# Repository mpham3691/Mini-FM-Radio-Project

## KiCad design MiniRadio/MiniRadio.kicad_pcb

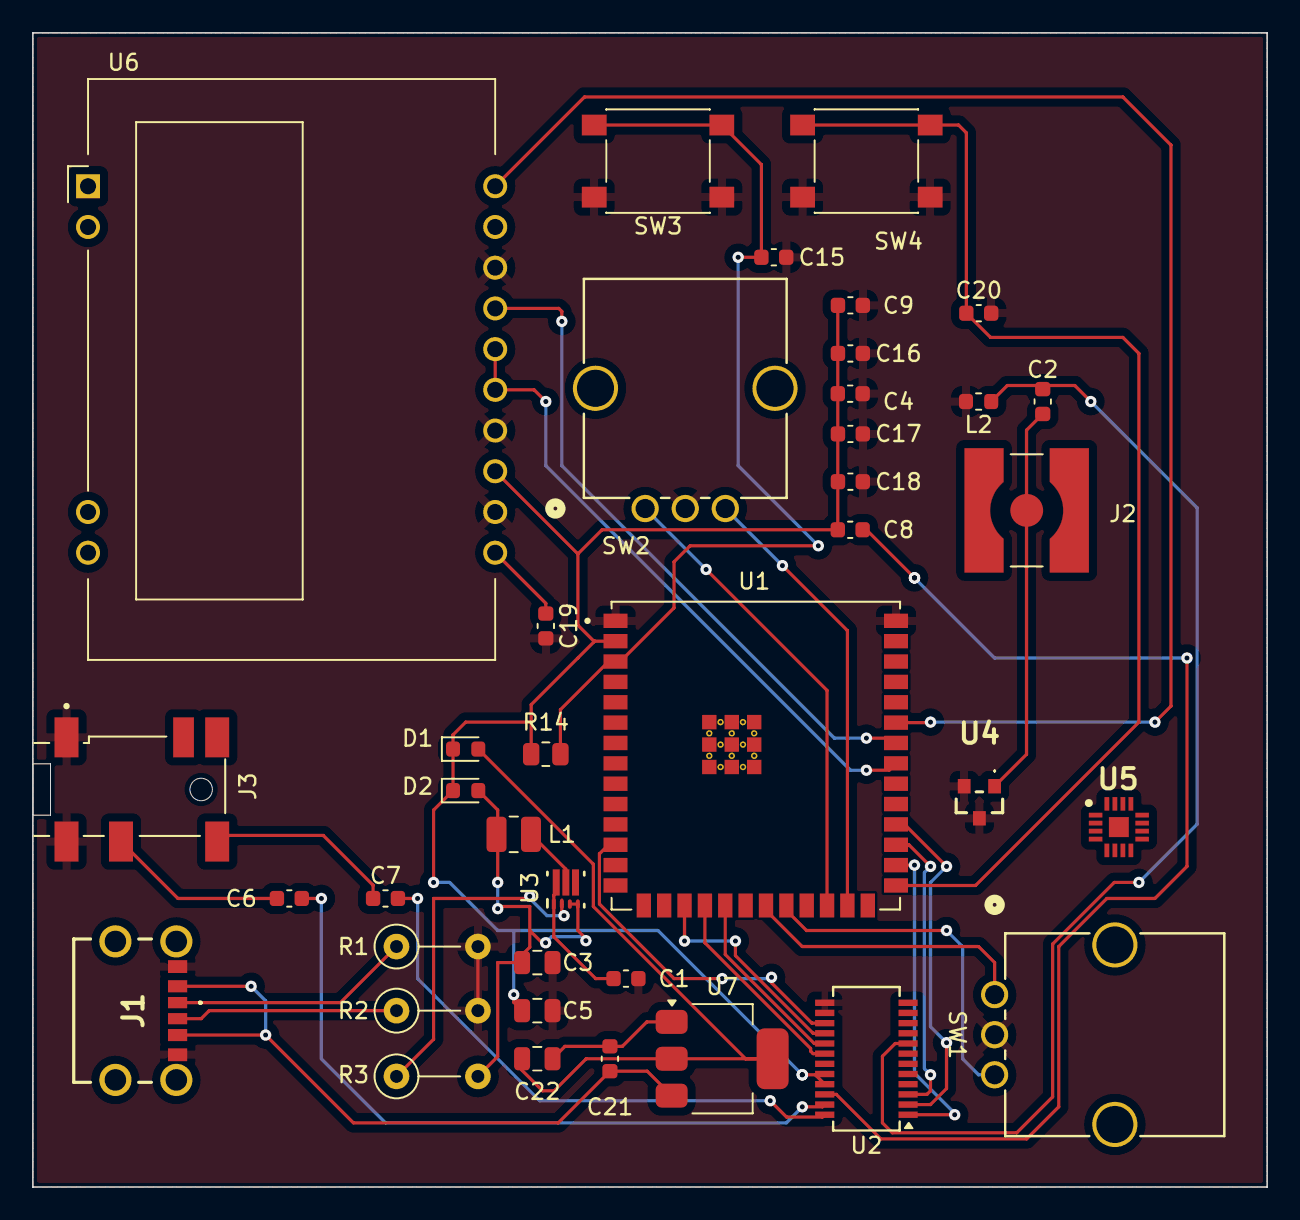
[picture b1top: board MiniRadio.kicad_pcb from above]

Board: 2 copper layers, 77.0 x 72.0 mm, 39 parts (0 on the bottom side), 35 nets.

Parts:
C1: 10u; C_0603_1608Metric
C2: 1n; C_0603_1608Metric
C3: 22u; C_0805_2012Metric
C4, C15, C17, C20: 0.1u; C_0603_1608Metric
C5, C22: 10u; C_0805_2012Metric
C6, C7: 4.7u; C_0603_1608Metric
C8: 22n; C_0603_1608Metric
C9, C21: 100n; C_0603_1608Metric
C16, C18, C19: 1u; C_0603_1608Metric
D1, D2: D_Schottky; D_0603_1608Metric
J1: USB_C_Receptacle_USB2.0; 2171750001
J2: SMA; LINX_CONSMA002-SMD-G-T
J3: 54-00178; TENSILITY_54-00178
L1: 470n; L_1008_2520Metric
L2: 56n; L_0603_1608Metric
R1, R2: 5.1k; R_Axial_DIN0207_L6.3mm_D2.5mm_P5.08mm_Vertical
R3: 1M; R_Axial_DIN0207_L6.3mm_D2.5mm_P5.08mm_Vertical
R14: 10k; R_0805_2012Metric
SW1: Freq_Tune; PEC12R-4XXXF-NXXXX_BRN
SW2: Volume_Tune; PEC12R-4XXXF-NXXXX_BRN
SW3: Reset; SW_SPST_PTS645
SW4: Boot; SW_SPST_PTS645
U1: ESP32-S3-WROOM-1; XCVR_ESP32-S3-WROOM-1U-N4
U2: Si4735-D60-GU; SSOP-24_3.9x8.7mm_P0.635mm
U3: RLT0007A
U4: D1213A01SO7
U5: QFN50P300X300X80-17N
U6: EA_DOGS164-A; EA_DOGS104X-A
U7: LD1117S33TR_SOT223; SOT-223-3_TabPin2

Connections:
+3.3V: C4.1, C5.1, C8.2, C9.1, C16.1, C17.1, C18.1, D1.1 (K), D2.1 (K), R14.1, U1.2 (3V3), U2.20 (VD), U2.21 (VA), U6.13 (VDD)
+5V: C21.1, J1.A9 (VBUS), J1.B9 (VBUS), U7.3 (VI)
/BATT_SUPPLY: C3.1, D2.2 (A), L1.2, R3.2, U3.3 (FB), U3.4 (VOS)
/DFS_RADIO: U1.30 (SPIDQS/GPIO37/FSPIQ/SUBSPIQ), U2.2 (DFS)
/DOUT_RADIO: U1.28 (SPIIO6/GPIO35/FSPID/SUBSPID), U2.1 (DOUT)
/FMI: C2.2, L2.1, U2.8 (FMI)
/FREQ_A: SW1.A, U1.21 (GPIO13/TOUCH13/ADC2_CH2/FSPIQ/FSPIIO7/S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)
/FREQ_B: SW1.B, U1.22 (GPIO14/TOUCH14/ADC2_CH3/FSPIWP/FSPIDQS/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)
/GPO3_RADIO: U1.29 (SPIIO7/GPIO36/FSPICLK/SUBSPICLK), U2.3 (GPO3/[DCLK])
/LOUT: C7.2, U2.24 (LOUT/[DFS])
/ROUT: C6.2, U2.23 (ROUT/[DOUT])
/RST_LCD: U1.35 (MTMS/GPIO42), U6.20 (~RST)
/RST_RADIO: U1.12 (GPIO8/TOUCH8/ADC1_CH7/SUBSPICS1), U2.15 (~RST)
/SCLK_LCD: U1.34 (MTDI/GPIO41/CLK_OUT1), U6.17 (SCLK)
/SCLK_RADIO: U1.19 (GPIO11/TOUCH11/ADC2_CH0/FSPID/FSPIIO5/S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), U2.17 (SCLK)
/SDIO_LCD: U1.33 (MTDO/GPIO40/CLK_OUT2), U6.15 (SOD), U6.16 (SID)
/SDIO_RADIO: U1.18 (GPIO10/TOUCH10/ADC1_CH9/FSPICS0/FSPIIO4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), U2.18 (SDIO)
/SEN_RADIO: U1.17 (GPIO9/TOUCH9/ADC1_CH8/FSPIHD/SUBSPIHD), U2.16 (~SEN)
/USB_SUPPLY: C22.1, D1.2 (A), U7.2 (VO)
/VOL_A: SW2.A, U1.24 (GPIO47/SPICLK_P/SUBSPICLK_P_DIFF)
/VOL_B: SW2.B, U1.25 (GPIO48/SPICLK_N/SUBSPICLK_N_DIFF)
/V_BATT: C1.1, U3.1 (EN), U3.7 (VIN)
GND: C1.2, C3.2, C4.2, C5.2, C9.2, C15.1, C16.2, C17.2, C18.2, C19.2, C20.2, J1.A12 (GND), J1.B12 (GND), J3.1, J3.2, L2.2, R1.2, R2.2, SW1.C, SW2.C, SW3.1, SW4.2, U1.1 (GND), U1.40 (GND), U2.13 (GND), U2.14 (GND), U3.5 (GND), U4.2 (VP), U4.3 (VN), U6.12 (IM1), U6.14 (VSS), U6.18 (~CS)
unnamed: C6.1, J3.3
unnamed: C7.1, J3.4
unnamed: J1.A5 (CC1), R1.1
unnamed: J1.B5 (CC2), R2.1
unnamed: C2.1, J2.1 (In), U4.1 (CH1)
unnamed: C15.2, R14.2, SW3.2, U1.3 (EN)
unnamed: C20.1, SW4.1, U1.27 (GPIO0/BOOT)
unnamed: C8.1, U2.22 (DBYP)
unnamed: R3.1, U3.2 (PG)
unnamed: L1.1, U3.6 (SW)
unnamed: C19.1, U6.11 (VOUT)
unnamed: C21.2, C22.2, U7.1 (GND)

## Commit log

2024-11-02 almost finishsed pcb layout
